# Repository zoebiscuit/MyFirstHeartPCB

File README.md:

My project is a pcb board with LED lights blinking on a timer. 

I made this project to explore my interest in hardware. I also did this to attempt to do the Sleepover + Stasis challenge. I purposefully did not submit this to Stasis.

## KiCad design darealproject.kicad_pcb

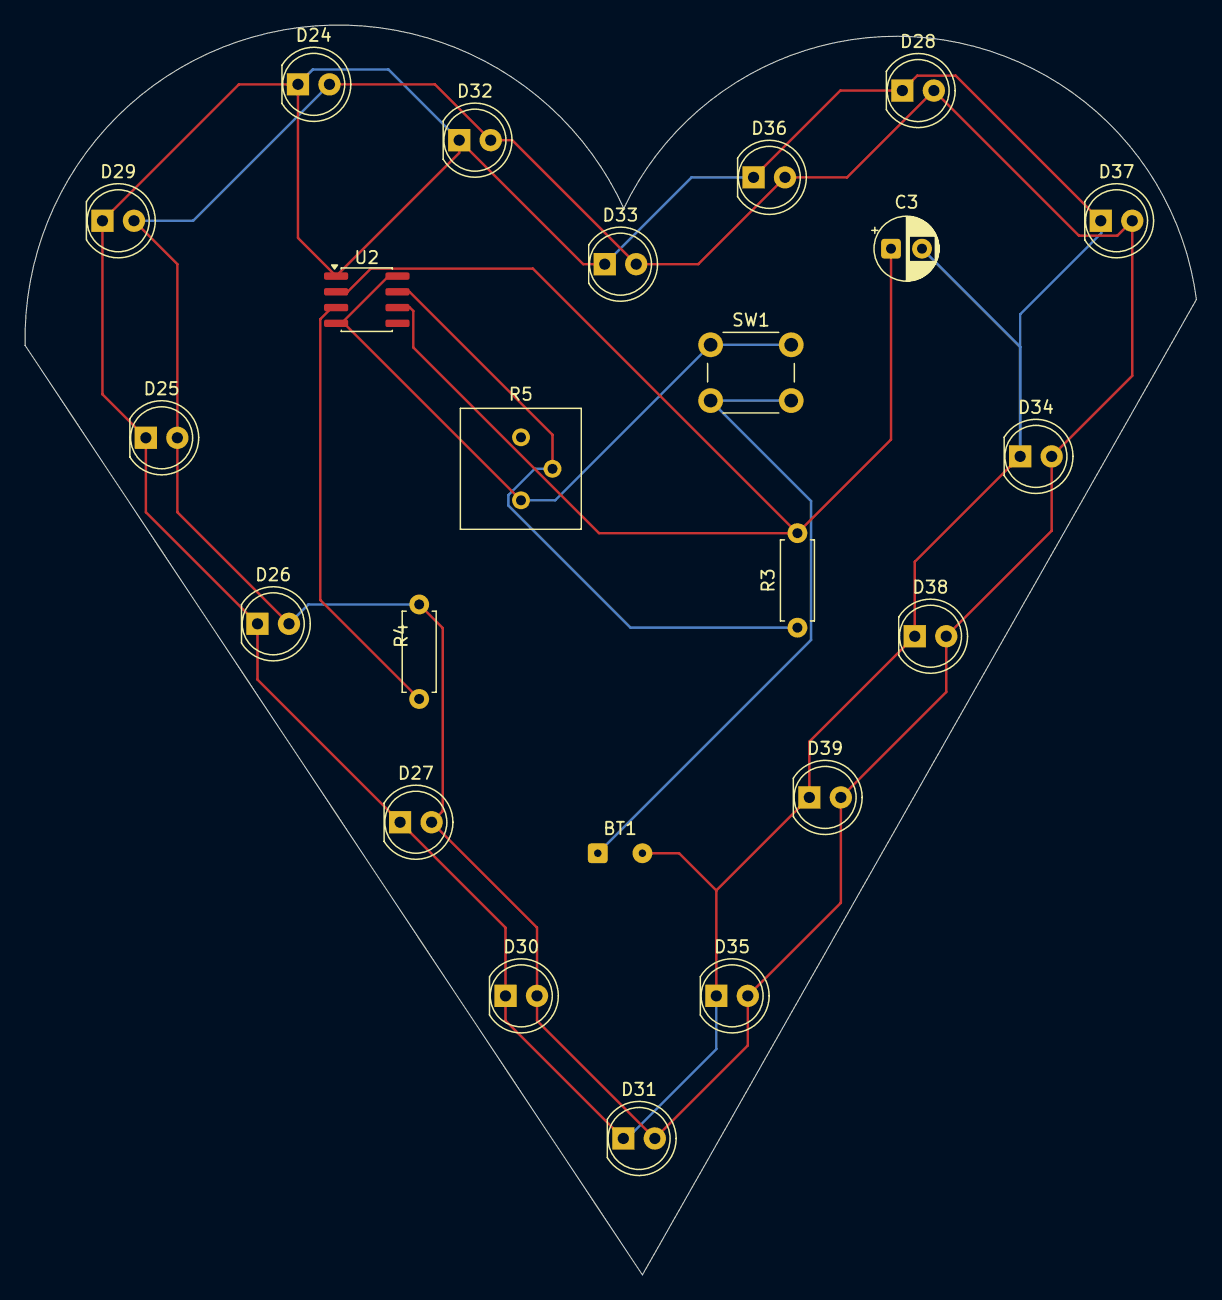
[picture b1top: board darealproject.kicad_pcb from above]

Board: 2 copper layers, 94.4 x 100.8 mm, 23 parts (0 on the bottom side), 7 nets.

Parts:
BT1: Battery; SolderWire-0.1sqmm_1x02_P3.6mm_D0.4mm_OD1mm
C3: C_Polarized; CP_Radial_D5.0mm_P2.50mm
D24, D25, D26, D27, D28, D29, D30, D31, D32, D33, D34, D35, D36, D37, D38, D39: LED; LED_D5.0mm
R3, R4: R; R_Axial_DIN0207_L6.3mm_D2.5mm_P7.62mm_Horizontal
R5: R_Variable; Potentiometer_Bourns_3386P_Vertical
SW1: SW_Push; SW_PUSH_6mm
U2: ICM7555xB; SOIC-8_3.9x4.9mm_P1.27mm

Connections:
GND: BT1.2 (-), C3.2, D24.1 (K), D25.1 (K), D26.1 (K), D27.1 (K), D28.1 (K), D29.1 (K), D30.1 (K), D31.1 (K), D32.1 (K), D33.1 (K), D34.1 (K), D35.1 (K), D36.1 (K), D37.1 (K), D38.1 (K), D39.1 (K), U2.1 (GND)
unnamed: BT1.1 (+), SW1.2
unnamed: R3.1, R5.2, U2.7 (DISCH)
unnamed: R4.1, U2.3 (OUT)
unnamed: C3.1, R3.2, U2.2 (TRIG), U2.6 (THRES)
unnamed: R5.1, SW1.1, U2.4 (~RST), U2.8 (VCC)
TOUT: D24.2 (A), D25.2 (A), D26.2 (A), D27.2 (A), D28.2 (A), D29.2 (A), D30.2 (A), D31.2 (A), D32.2 (A), D33.2 (A), D34.2 (A), D35.2 (A), D36.2 (A), D37.2 (A), D38.2 (A), D39.2 (A), R4.2

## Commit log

2026-04-05 My PCB Files
